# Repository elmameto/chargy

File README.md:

# chargy
Very small chargers for pretty small Lithium batteries

There are a tht and smd version. The smd has large pads, so you should
be able to handle solder it too.
Ordered the smd version online, will post photos as soon as it arrives :)

**_Will post more information as soon as I can_**

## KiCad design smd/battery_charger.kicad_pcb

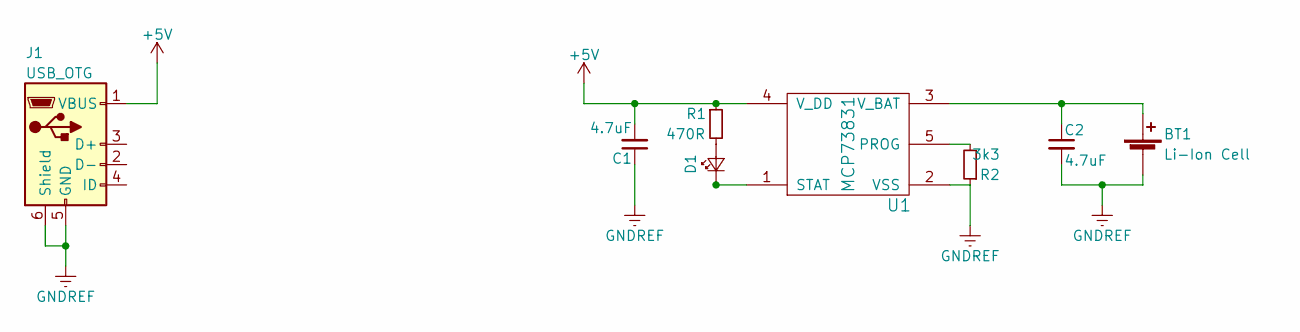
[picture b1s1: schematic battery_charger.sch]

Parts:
BT1: Li-Ion Cell; Socket_Strip_Straight_1x02
C1, C2: 4.7uF; C_0603_HandSoldering
D1: LED; LED_3528
J1: USB_OTG; MICRO-B_USB
R1: 470R; R_0603_HandSoldering
R2: 3k3; R_0603_HandSoldering
U1: MCP73831; SOT-23-5

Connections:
+5V: C1.2, J1.1 (VBUS), R1.1, U1.4 (V_DD)
GNDREF: BT1.2 (-), C1.1, C2.2, J1.5 (GND), J1.6 (Shield), R2.1, U1.2 (VSS)
unnamed: BT1.1 (+), C2.1, U1.3 (V_BAT)
unnamed: D1.1 (K), U1.1 (STAT)
unnamed: D1.2 (A), R1.2
unnamed: R2.2, U1.5 (PROG)

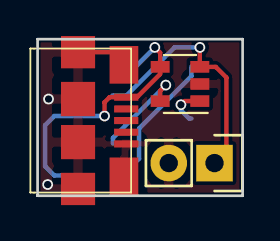
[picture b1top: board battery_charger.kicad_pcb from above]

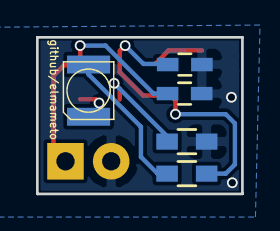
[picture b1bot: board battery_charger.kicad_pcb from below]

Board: 2 copper layers, 11.4 x 8.7 mm, 8 parts (5 on the bottom side), 6 nets.

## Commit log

2017-04-06 Made the board almost half as big as before
